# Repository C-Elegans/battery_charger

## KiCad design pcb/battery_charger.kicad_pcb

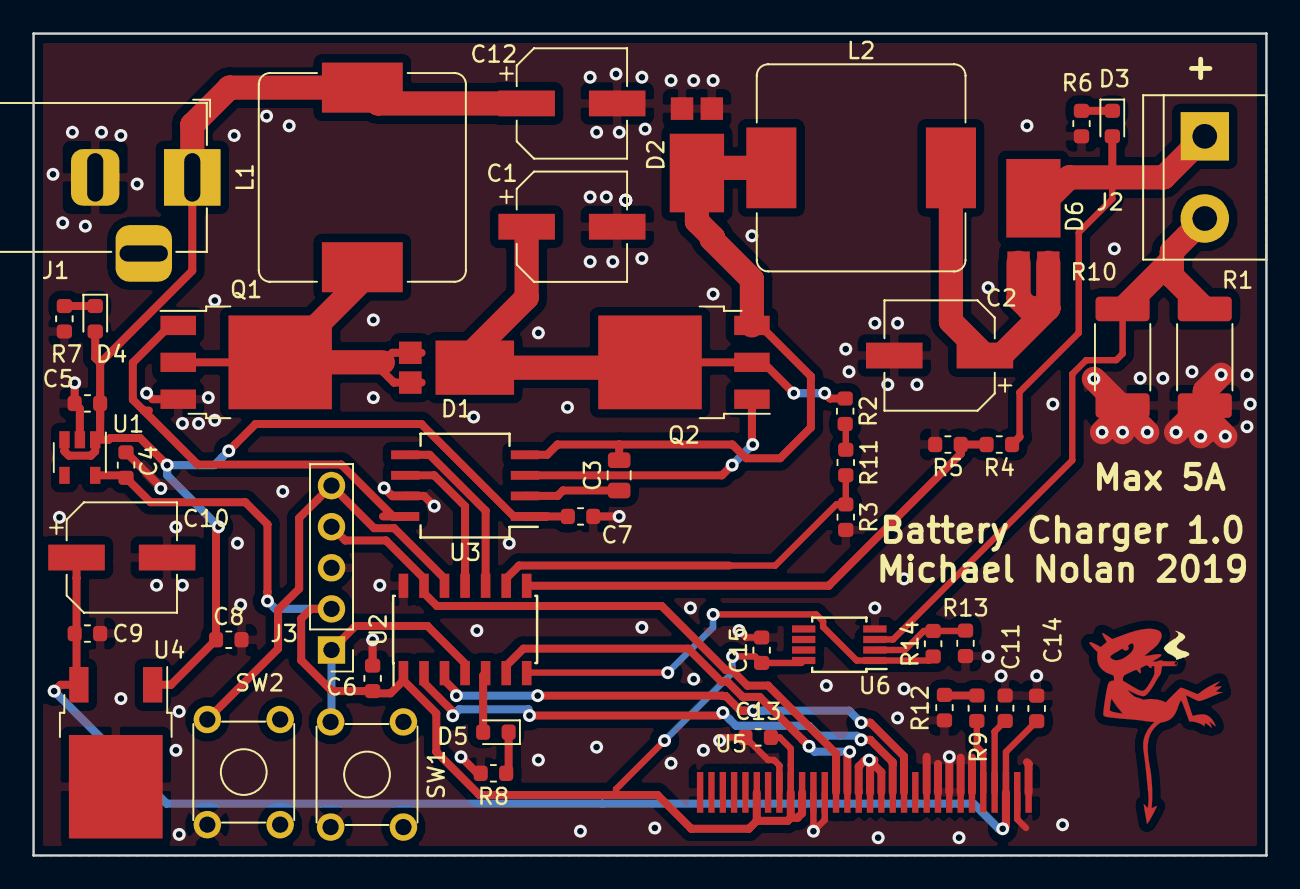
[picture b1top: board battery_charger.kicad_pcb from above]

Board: 2 copper layers, 76.2 x 50.8 mm, 50 parts (0 on the bottom side), 33 nets.

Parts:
C1, C2, C10, C12: 20uF; CP_Elec_6.3x5.4
C3: 100n; C_0805_2012Metric
C4, C11, C13, C14, C15: 100n; C_0603_1608Metric
C5, C9: 330n; C_0603_1608Metric
C6, C8: 1u; C_0603_1608Metric
C7: 3.3u; C_0603_1608Metric
D1, D2, D6: D_Schottky; PowerDI5
D3, D4, D5: LED; LED_0603_1608Metric
J1: Barrel_Jack; BarrelJack_Horizontal
J2: Screw_Terminal_01x02; TerminalBlock_bornier-2_P5.08mm
J3: Conn_01x05_Male; PinHeader_1x05_P2.54mm_Vertical
L1: 15uH; L_Bourns_SRP1245A
L2: 10uH; L_Bourns_SRP1245A
Q1, Q2: Q_NMOS_GDSD; TO-252-3_TabPin4
R1, R10: 0.1; R_2512_6332Metric_Pad1.52x3.35mm_HandSolder
R2, R4, R11, R12: 10k; R_0603_1608Metric
R3, R5: 1k; R_0603_1608Metric
R6, R7, R13: 2k; R_0603_1608Metric
R8: 300; R_0603_1608Metric
R9: 750k; R_0603_1608Metric
R14: 15k; R_0603_1608Metric
SW1, SW2: SW_Push_Dual; SW_TH_Tactile_Omron_B3F-10xx
U1: AP2127K-3.3; SOT-23-5
U2: PIC16f1574; SOIC-14_3.9x8.7mm_P1.27mm
U3: mcp4604; SO-8_5.3x6.2mm_P1.27mm
U4: LF90_TO252; TO-252-2
U5: ER-OLED; ffc_0.60mmx30
U6: TL072; MSOP-8_3x3mm_P0.65mm

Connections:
+3V3: C4.1, C6.1, C13.1, C15.1, J3.2, U1.5, U2.1, U5.6, U5.9, U5.10, U6.8
+9V: C9.1, C10.1, C14.1, U4.3, U5.28
+12V: C5.1, C7.1, C8.1, C12.1, D4.2, J1.1, L1.2, U1.1, U1.3, U3.1, U4.1
+BATT: D3.2, D6.1, J2.1, R4.1
-BATT: J2.2, R1.1, R10.1, U6.3
/batt_sense: R4.2, R5.1, U2.8
/boost_ctrl: U2.11, U3.6
/boost_gate: Q1.1, U3.8
/boost_sense: R3.1, R11.2, U2.9
/buck_ctrl: U2.10, U3.5
/buck_gate: Q2.1, U3.3
/buck_source: C3.2, D2.1, L2.1, Q2.3, U3.4
/chrg_led: D5.2, U2.5
/icspclk: J3.5, SW2.3, U2.12
/icspdat: J3.4, U2.13, U5.13
/isense: R14.1, U2.7, U6.1
/mclr: J3.1, SW1.3, U2.4
/mosi: U2.3, U5.19
/pwr_boost_drain: D1.2, L1.1, Q1.2, Q1.4
/reset_n: U2.6, U5.14
/sck: U2.2, U5.18
/vboost: C1.1, D1.1, Q2.2, Q2.4, R2.1
GND: C1.2, C2.2, C4.2, C5.2, C6.2, C7.2, C8.2, C9.2, C10.2, C11.2, C12.2, C13.2, C14.2, C15.2, D2.2, J1.2, J3.3, Q1.3, R1.2, R3.2, R5.2, R6.2, R7.2, R8.2, R10.2, R12.2, R13.1, SW1.4, SW2.4, U1.2, U2.14, U3.7, U4.2, U5.1, U5.8, U5.11, U5.12, U5.15, U5.16, U5.17, U5.21, U5.22, U5.23, U5.24, U5.25, U5.29, U5.30, U6.4
unnamed: C2.1, D6.2, L2.2
unnamed: C3.1, U3.2
unnamed: C11.1, U5.27
unnamed: D3.1, R6.1
unnamed: D4.1, R7.1
unnamed: D5.1, R8.1
unnamed: R9.1, U5.26
unnamed: R2.2, R11.1
unnamed: R9.2, R12.1
unnamed: R13.2, R14.2, U6.2
